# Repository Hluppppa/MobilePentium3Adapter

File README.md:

# Mobile Pentium 3 Adapter
An attempt to recreate an adapter for Pentium 3 mobile processors to socket 370 (bga495 -> pga370) by reverse engineering existed one.

Now you can install XBOX-Original's CPU in normal desktop :D

Core Voltage (VCC) table:
| VID3 | VID2 | VID1 | VID0 | VCC  |
| ----| ----| ----| ----| ---- |
| 1-2 | 1-2 | 1-2 | 1-2 | 1.30 |
| 1-2 | 1-2 | 1-2 | 2-3 | 1.35 |
| 1-2 | 1-2 | 2-3 | 1-2 | 1.40 |
| 1-2 | 1-2 | 2-3 | 2-3 | 1.45 |
| 1-2 | 2-3 | 1-2 | 1-2 | 1.50 |
| 1-2 | 2-3 | 1-2 | 2-3 | 1.55 |
| 1-2 | 2-3 | 2-3 | 1-2 | 1.60 |
| 1-2 | 2-3 | 2-3 | 2-3 | 1.65 |
| 2-3 | 1-2 | 1-2 | 1-2 | 1.70 |
| 2-3 | 1-2 | 1-2 | 2-3 | 1.75 |
| 2-3 | 1-2 | 2-3 | 1-2 | 1.80 |
| 2-3 | 1-2 | 2-3 | 2-3 | 1.85 |
| 2-3 | 2-3 | 1-2 | 1-2 | 1.90 |
| 2-3 | 2-3 | 1-2 | 2-3 | 1.95 |
| 2-3 | 2-3 | 2-3 | 1-2 | 2.00 |
| 2-3 | 2-3 | 2-3 | 2-3 | 2.05 |

ATTENTION! This adapter is still in development and has not been tested yet!

Made with KiCad 12.05.2024

Links:

https://download.intel.com/design/PentiumIII/datashts/24526408.pdf

https://datasheet.octopart.com/KC80526LY500256SL4JP-Intel-datasheet-125284.pdf

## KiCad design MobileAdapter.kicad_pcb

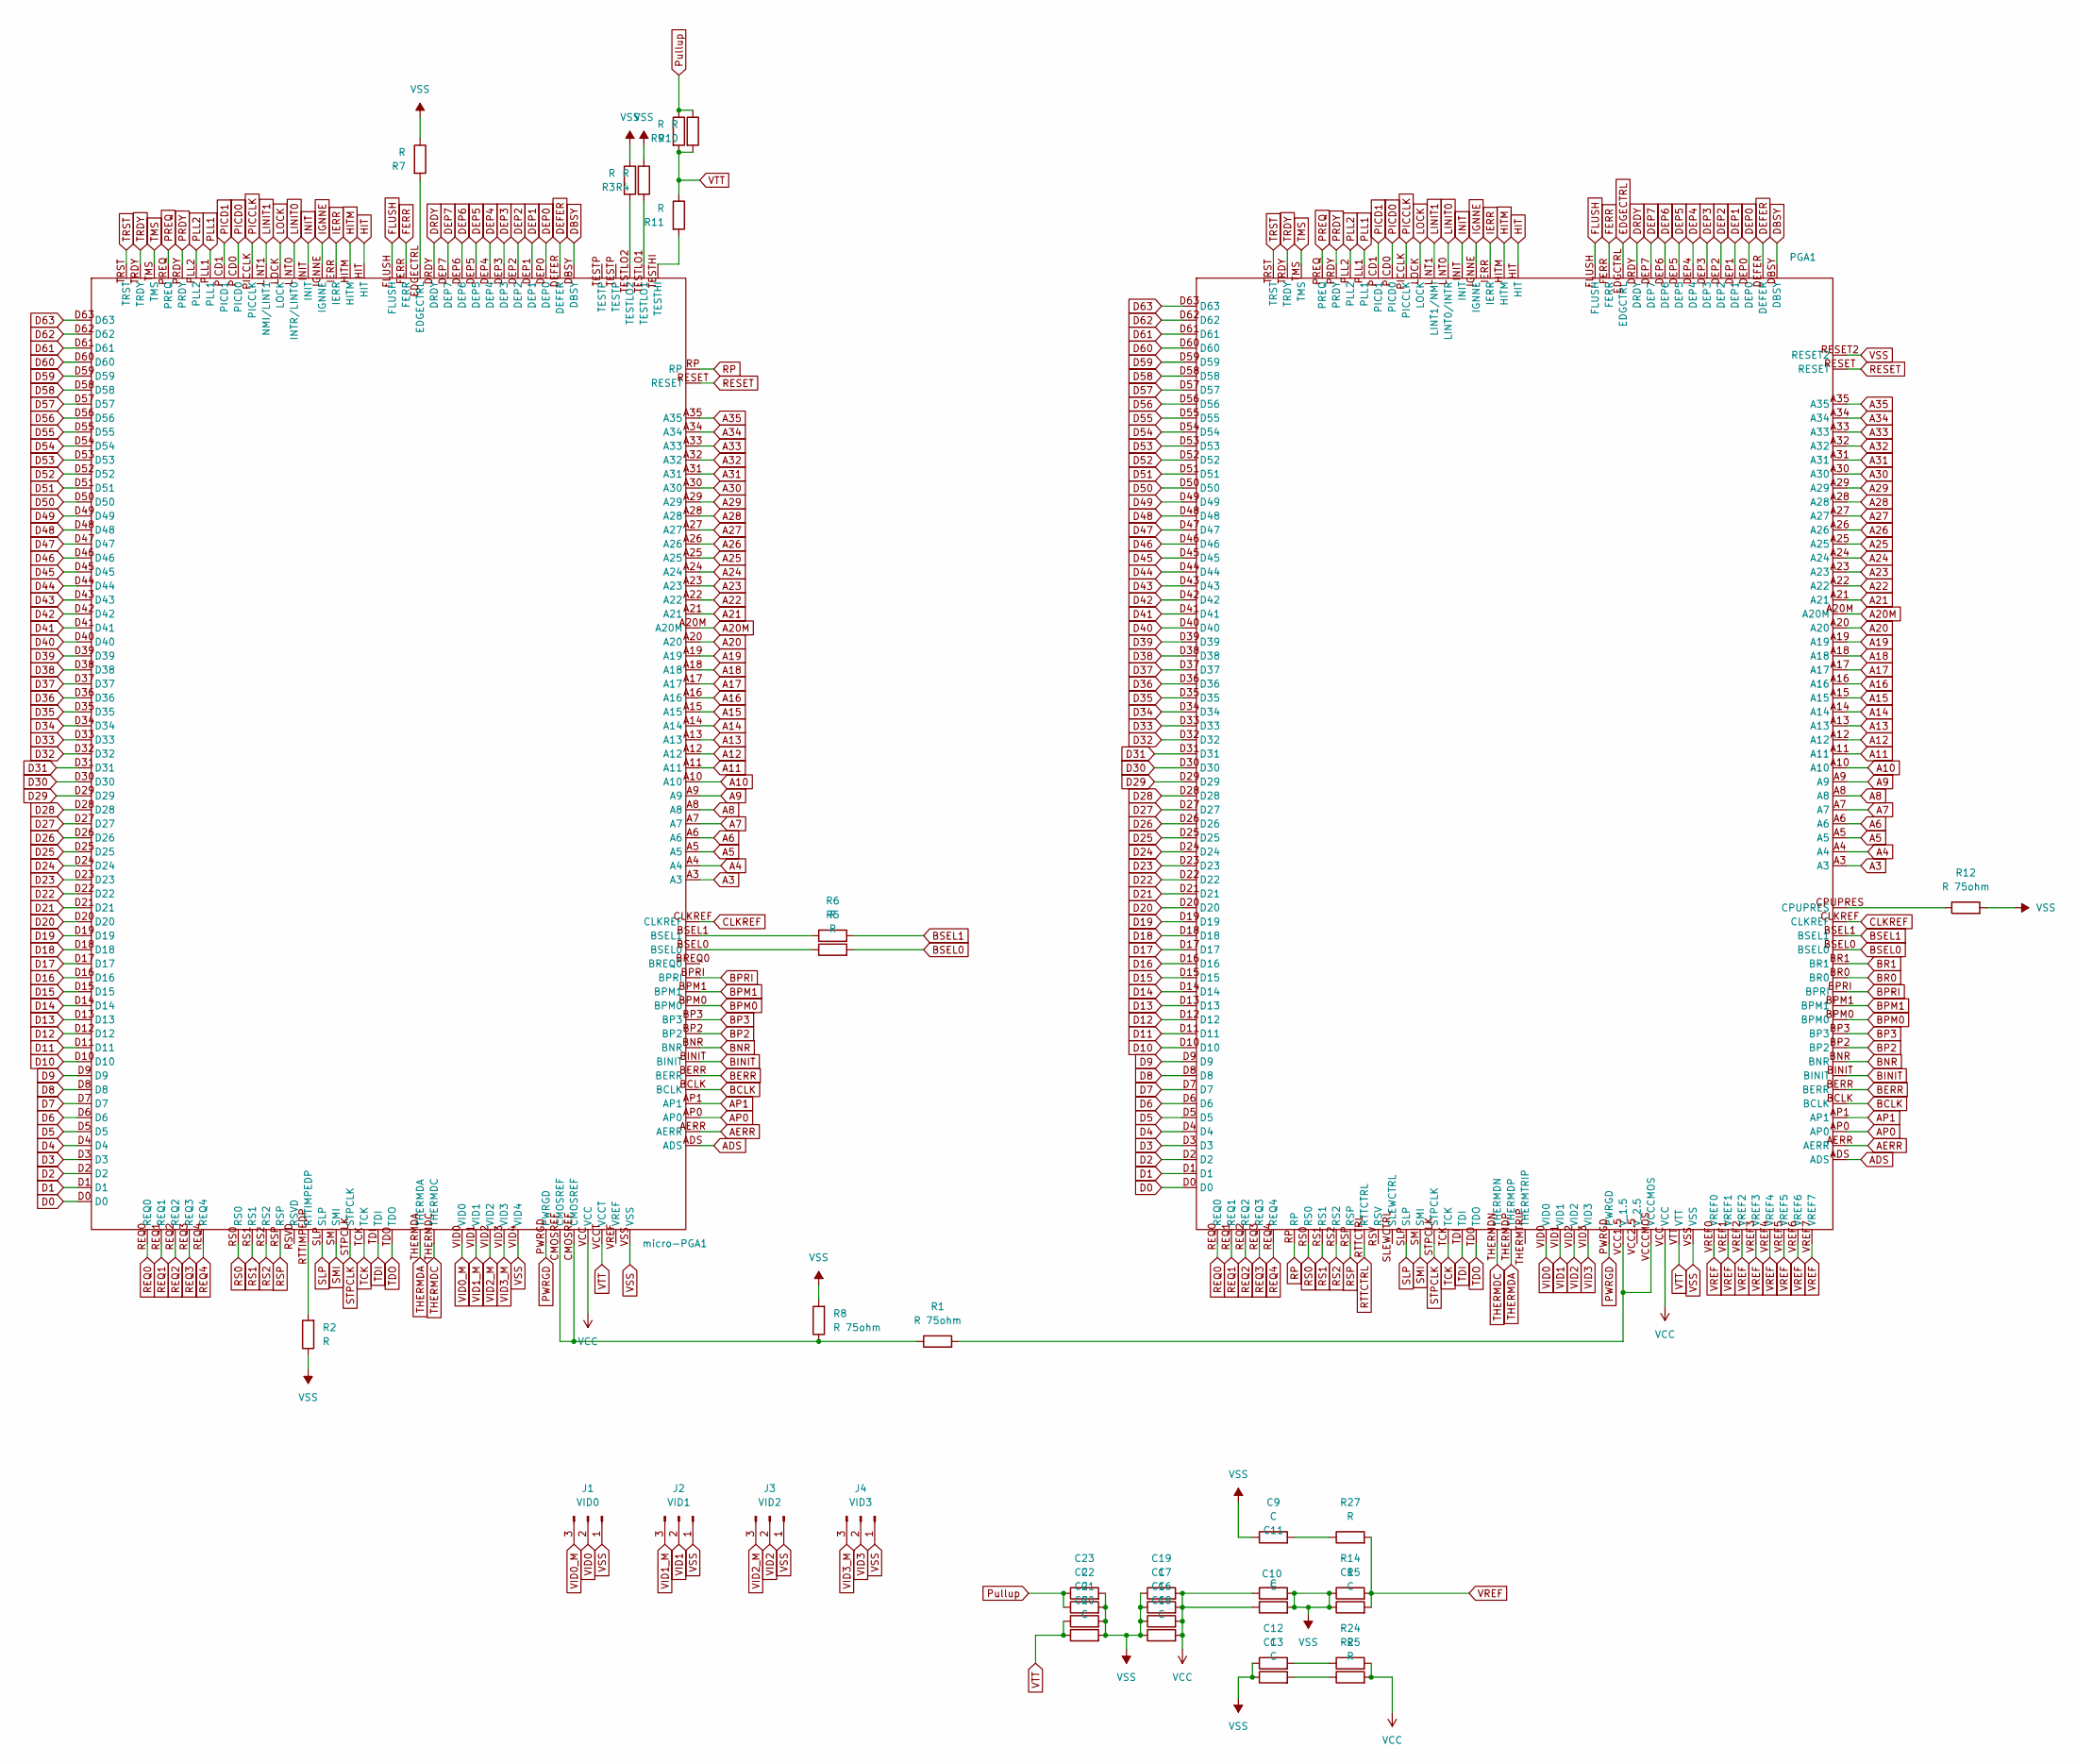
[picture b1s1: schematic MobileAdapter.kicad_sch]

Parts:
C9, C10, C11, C12, C13, C15, C16, C17, C18, C19, C20, C21: C; C_0805_2012Metric
C22, C23: C; C_0603_1608Metric
J1: VID0; PinHeader_1x03_P1.27mm_Vertical
J2: VID1; PinHeader_1x03_P1.27mm_Vertical
J3: VID2; PinHeader_1x03_P1.27mm_Vertical
J4: VID3; PinHeader_1x03_P1.27mm_Vertical
PGA1: pga370
R1, R8, R12: R 75ohm; C_0603_1608Metric
R2, R3, R4, R5, R6, R7, R9, R10, R11, R24, R25, R27: R; C_0603_1608Metric
R14: R; C_0805_2012Metric
micro-PGA1: bga495

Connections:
A3: PGA1.A3, micro-PGA1.A3
A4: PGA1.A4, micro-PGA1.A4
A5: PGA1.A5, micro-PGA1.A5
A6: PGA1.A6, micro-PGA1.A6
A7: PGA1.A7, micro-PGA1.A7
A8: PGA1.A8, micro-PGA1.A8
A9: PGA1.A9, micro-PGA1.A9
A10: PGA1.A10, micro-PGA1.A10
A11: PGA1.A11, micro-PGA1.A11
A12: PGA1.A12, micro-PGA1.A12
A13: PGA1.A13, micro-PGA1.A13
A14: PGA1.A14, micro-PGA1.A14
A15: PGA1.A15, micro-PGA1.A15
A16: PGA1.A16, micro-PGA1.A16
A17: PGA1.A17, micro-PGA1.A17
A18: PGA1.A18, micro-PGA1.A18
A19: PGA1.A19, micro-PGA1.A19
A20: PGA1.A20, micro-PGA1.A20
A20M: PGA1.A20M, micro-PGA1.A20M
A21: PGA1.A21, micro-PGA1.A21
A22: PGA1.A22, micro-PGA1.A22
A23: PGA1.A23, micro-PGA1.A23
A24: PGA1.A24, micro-PGA1.A24
A25: PGA1.A25, micro-PGA1.A25
A26: PGA1.A26, micro-PGA1.A26
A27: PGA1.A27, micro-PGA1.A27
A28: PGA1.A28, micro-PGA1.A28
A29: PGA1.A29, micro-PGA1.A29
A30: PGA1.A30, micro-PGA1.A30
A31: PGA1.A31, micro-PGA1.A31
A32: PGA1.A32, micro-PGA1.A32
A33: PGA1.A33, micro-PGA1.A33
A34: PGA1.A34, micro-PGA1.A34
A35: PGA1.A35, micro-PGA1.A35
ADS: PGA1.ADS, micro-PGA1.ADS
AERR: PGA1.AERR, micro-PGA1.AERR
AP0: PGA1.AP0, micro-PGA1.AP0
AP1: PGA1.AP1, micro-PGA1.AP1
BCLK: PGA1.BCLK, micro-PGA1.BCLK
BERR: PGA1.BERR, micro-PGA1.BERR
BINIT: PGA1.BINIT, micro-PGA1.BINIT
BNR: PGA1.BNR, micro-PGA1.BNR
BP2: PGA1.BP2, micro-PGA1.BP2
BP3: PGA1.BP3, micro-PGA1.BP3
BPM0: PGA1.BPM0, micro-PGA1.BPM0
BPM1: PGA1.BPM1, micro-PGA1.BPM1
BPRI: PGA1.BPRI, micro-PGA1.BPRI
BR0: PGA1.BR0
BR1: PGA1.BR1
BSEL0: PGA1.BSEL0, R5.2
BSEL1: PGA1.BSEL1, R6.2
CLKREF: PGA1.CLKREF, micro-PGA1.CLKREF
D0: PGA1.D0, micro-PGA1.D0
D1: PGA1.D1, micro-PGA1.D1
D2: PGA1.D2, micro-PGA1.D2
D3: PGA1.D3, micro-PGA1.D3
D4: PGA1.D4, micro-PGA1.D4
D5: PGA1.D5, micro-PGA1.D5
D6: PGA1.D6, micro-PGA1.D6
D7: PGA1.D7, micro-PGA1.D7
D8: PGA1.D8, micro-PGA1.D8
D9: PGA1.D9, micro-PGA1.D9
D10: PGA1.D10, micro-PGA1.D10
D11: PGA1.D11, micro-PGA1.D11
D12: PGA1.D12, micro-PGA1.D12
D13: PGA1.D13, micro-PGA1.D13
D14: PGA1.D14, micro-PGA1.D14
D15: PGA1.D15, micro-PGA1.D15
D16: PGA1.D16, micro-PGA1.D16
D17: PGA1.D17, micro-PGA1.D17
D18: PGA1.D18, micro-PGA1.D18
D19: PGA1.D19, micro-PGA1.D19
D20: PGA1.D20, micro-PGA1.D20
D21: PGA1.D21, micro-PGA1.D21
D22: PGA1.D22, micro-PGA1.D22
D23: PGA1.D23, micro-PGA1.D23
D24: PGA1.D24, micro-PGA1.D24
D25: PGA1.D25, micro-PGA1.D25
D26: PGA1.D26, micro-PGA1.D26
D27: PGA1.D27, micro-PGA1.D27
D28: PGA1.D28, micro-PGA1.D28
D29: PGA1.D29, micro-PGA1.D29
D30: PGA1.D30, micro-PGA1.D30
D31: PGA1.D31, micro-PGA1.D31
D32: PGA1.D32, micro-PGA1.D32
D33: PGA1.D33, micro-PGA1.D33
D34: PGA1.D34, micro-PGA1.D34
D35: PGA1.D35, micro-PGA1.D35
D36: PGA1.D36, micro-PGA1.D36
D37: PGA1.D37, micro-PGA1.D37
D38: PGA1.D38, micro-PGA1.D38
D39: PGA1.D39, micro-PGA1.D39
D40: PGA1.D40, micro-PGA1.D40
D41: PGA1.D41, micro-PGA1.D41
D42: PGA1.D42, micro-PGA1.D42
D43: PGA1.D43, micro-PGA1.D43
D44: PGA1.D44, micro-PGA1.D44
D45: PGA1.D45, micro-PGA1.D45
D46: PGA1.D46, micro-PGA1.D46
D47: PGA1.D47, micro-PGA1.D47
D48: PGA1.D48, micro-PGA1.D48
D49: PGA1.D49, micro-PGA1.D49
D50: PGA1.D50, micro-PGA1.D50
D51: PGA1.D51, micro-PGA1.D51
D52: PGA1.D52, micro-PGA1.D52
D53: PGA1.D53, micro-PGA1.D53
D54: PGA1.D54, micro-PGA1.D54
D55: PGA1.D55, micro-PGA1.D55
D56: PGA1.D56, micro-PGA1.D56
D57: PGA1.D57, micro-PGA1.D57
D58: PGA1.D58, micro-PGA1.D58
D59: PGA1.D59, micro-PGA1.D59
D60: PGA1.D60, micro-PGA1.D60
D61: PGA1.D61, micro-PGA1.D61
D62: PGA1.D62, micro-PGA1.D62
D63: PGA1.D63, micro-PGA1.D63
DBSY: PGA1.DBSY, micro-PGA1.DBSY
DEFER: PGA1.DEFER, micro-PGA1.DEFER
DEP0: PGA1.DEP0, micro-PGA1.DEP0
DEP1: PGA1.DEP1, micro-PGA1.DEP1
DEP2: PGA1.DEP2, micro-PGA1.DEP2
DEP3: PGA1.DEP3, micro-PGA1.DEP3
DEP4: PGA1.DEP4, micro-PGA1.DEP4
DEP5: PGA1.DEP5, micro-PGA1.DEP5
DEP6: PGA1.DEP6, micro-PGA1.DEP6
DEP7: PGA1.DEP7, micro-PGA1.DEP7
DRDY: PGA1.DRDY, micro-PGA1.DRDY
EDGECTRL: PGA1.EDGCTRL
FERR: PGA1.FERR, micro-PGA1.FERR
FLUSH: PGA1.FLUSH, micro-PGA1.FLUSH
HIT: PGA1.HIT, micro-PGA1.HIT
HITM: PGA1.HITM, micro-PGA1.HITM
IERR: PGA1.IERR, micro-PGA1.IERR
IGNNE: PGA1.IGNNE, micro-PGA1.IGNNE
INIT: PGA1.INIT, micro-PGA1.INIT
LINIT0: PGA1.LINT0 (LINT0/INTR), micro-PGA1.LINT0 (INTR/LINT0)
LINIT1: PGA1.LINT1 (LINT1/NMI), micro-PGA1.LINT1 (NMI/LINT1)
LOCK: PGA1.LOCK, micro-PGA1.LOCK
unnamed: C9.2, R27.1
unnamed: C12.2, R24.1
unnamed: C13.2, R25.1
unnamed: PGA1.CPUPRES, R12.1
unnamed: PGA1.VCC1.5 (V_1.5), PGA1.VCCCMOS, R1.2
unnamed: R1.1, R8.1, micro-PGA1.CMOSREF
unnamed: R2.2, micro-PGA1.RTTIMPEDP
unnamed: R3.2, micro-PGA1.TESTLO2
unnamed: R4.2, micro-PGA1.TESTLO1
unnamed: R5.1, micro-PGA1.BSEL0
unnamed: R6.1, micro-PGA1.BSEL1
unnamed: R7.2, micro-PGA1.EDGECTRL
unnamed: R11.2, micro-PGA1.TESTHI
PICCLK: PGA1.PICCLK, micro-PGA1.PICCLK
PICD0: PGA1.PICD0, micro-PGA1.PICD0
PICD1: PGA1.PICD1, micro-PGA1.PICD1
PLL1: PGA1.PLL1, micro-PGA1.PLL1
PLL2: PGA1.PLL2, micro-PGA1.PLL2
PRDY: PGA1.PRDY, micro-PGA1.PRDY
PREQ: PGA1.PREQ, micro-PGA1.PREQ
PWRGD: PGA1.PWRGD, micro-PGA1.PWRGD
Pullup: C22.1, C23.1, R9.1, R10.1
REQ0: PGA1.REQ0, micro-PGA1.REQ0
REQ1: PGA1.REQ1, micro-PGA1.REQ1
REQ2: PGA1.REQ2, micro-PGA1.REQ2
REQ3: PGA1.REQ3, micro-PGA1.REQ3
REQ4: PGA1.REQ4, micro-PGA1.REQ4
RESET: PGA1.RESET, micro-PGA1.RESET
RP: PGA1.RP, micro-PGA1.RP
RS0: PGA1.RS0, micro-PGA1.RS0
RS1: PGA1.RS1, micro-PGA1.RS1
RS2: PGA1.RS2, micro-PGA1.RS2
RSP: PGA1.RSP, micro-PGA1.RSP
RTTCTRL: PGA1.RTTCTRL
SLP: PGA1.SLP, micro-PGA1.SLP
SMI: PGA1.SMI, micro-PGA1.SMI
STPCLK: PGA1.STPCLK, micro-PGA1.STPCLK
TCK: PGA1.TCK, micro-PGA1.TCK
TDI: PGA1.TDI, micro-PGA1.TDI
TDO: PGA1.TDO, micro-PGA1.TDO
THERMDA: PGA1.THERMDP, micro-PGA1.THERMDA
THERMDC: PGA1.THERMDN, micro-PGA1.THERMDC
TMS: PGA1.TMS, micro-PGA1.TMS
TRDY: PGA1.TRDY, micro-PGA1.TRDY
TRST: PGA1.TRST, micro-PGA1.TRST
VCC: C10.1, C11.1, C16.2, C17.2, C18.2, C19.2, PGA1.VCC, R24.2, R25.2, micro-PGA1.VCC
VID0: J1.2, PGA1.VID0
VID0_M: J1.3, micro-PGA1.VID0
VID1: J2.2, PGA1.VID1
VID1_M: J2.3, micro-PGA1.VID1
VID2: J3.2, PGA1.VID2
VID2_M: J3.3, micro-PGA1.VID2
VID3: J4.2, PGA1.VID3
VID3_M: J4.3, micro-PGA1.VID3
VREF: C15.2, PGA1.VREF0, PGA1.VREF1, PGA1.VREF2, PGA1.VREF3, PGA1.VREF4, PGA1.VREF5, PGA1.VREF6, PGA1.VREF7, R14.2, R27.2
VSS: C9.1, C10.2, C11.2, C12.1, C13.1, C15.1, C16.1, C17.1, C18.1, C19.1, C20.2, C21.2, C22.2, C23.2, J1.1, J2.1, J3.1, J4.1, PGA1.RESET2, PGA1.VSS, R2.1, R3.1, R4.1, R7.1, R8.2, R12.2, R14.1, micro-PGA1.VID4, micro-PGA1.VSS
VTT: C20.1, C21.1, PGA1.VTT, R9.2, R10.2, R11.1, micro-PGA1.VCCT

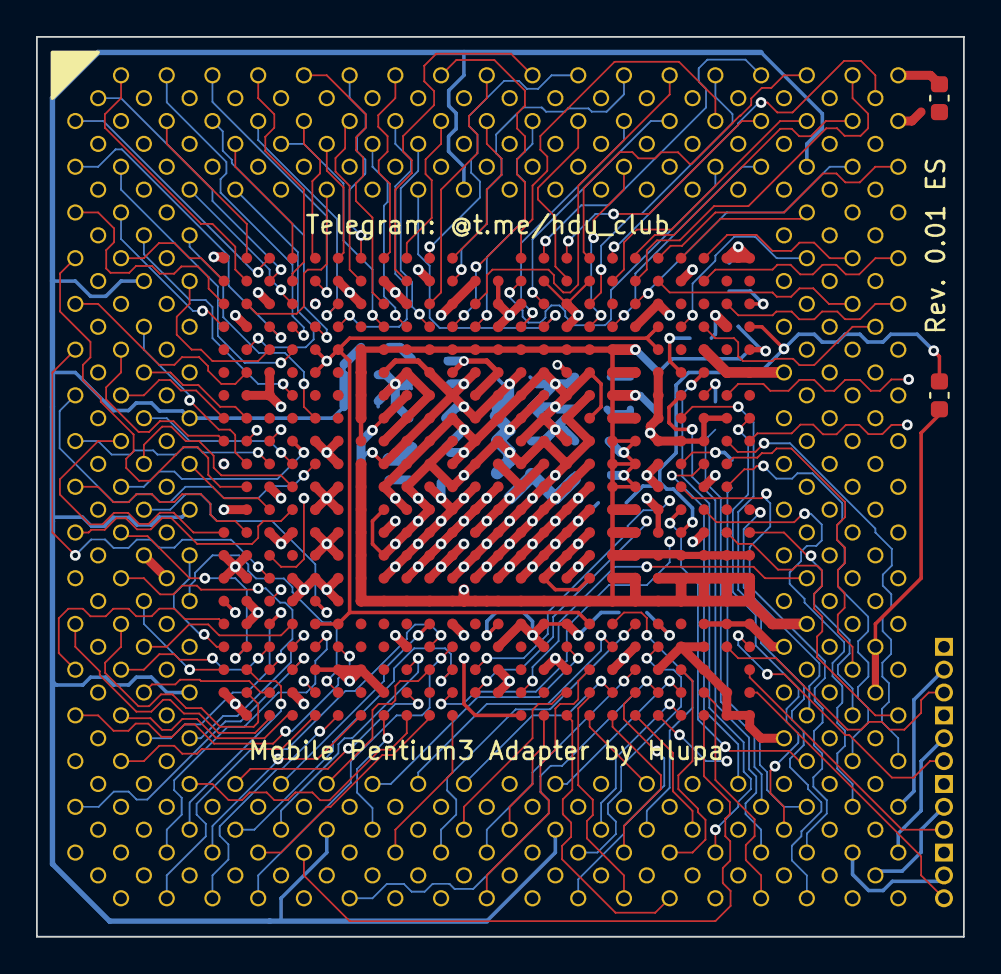
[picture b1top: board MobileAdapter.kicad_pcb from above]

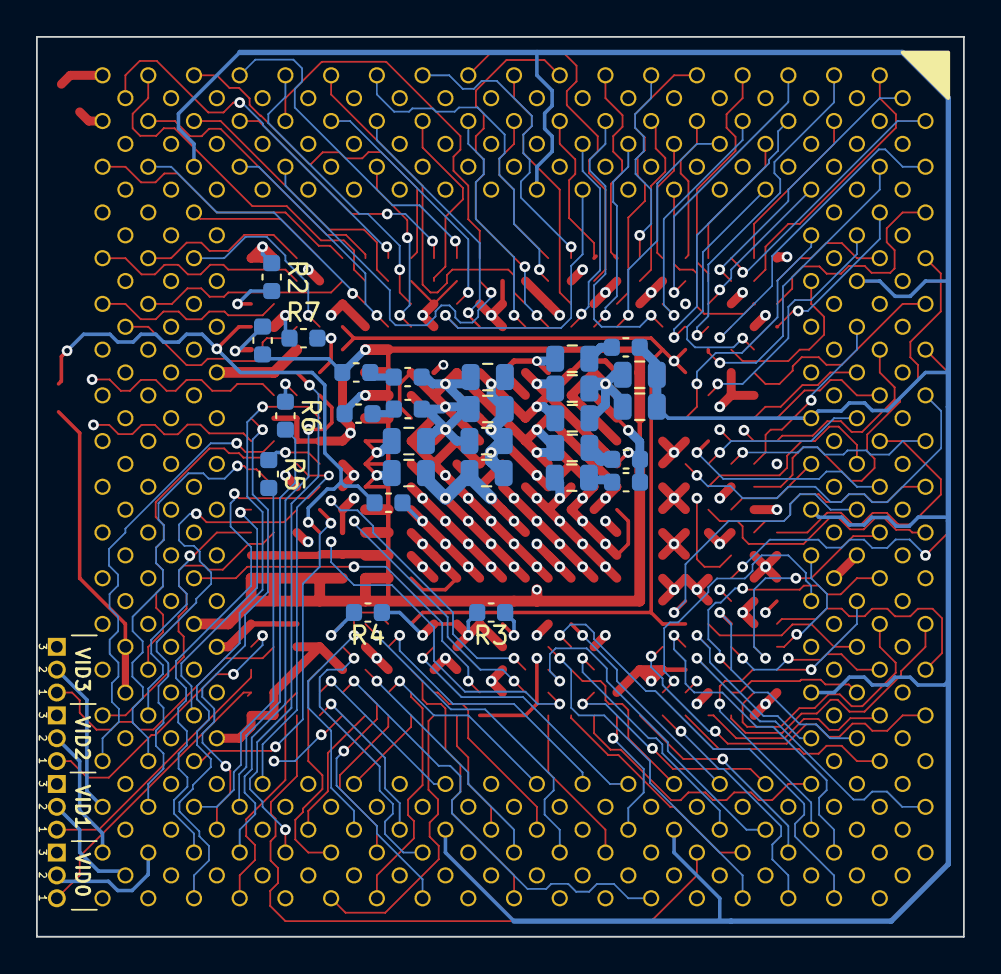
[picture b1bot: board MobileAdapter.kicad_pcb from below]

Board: 4 copper layers, 51.5 x 50.0 mm, 36 parts (29 on the bottom side), 191 nets.

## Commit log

2024-06-22 Adding GERBER file
2024-06-22 Added VCore table
2024-06-22 Fix grammar error
2024-07-13 Trace and Silk fix
